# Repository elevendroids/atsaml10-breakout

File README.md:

# ATSAML1x Breakout Board (Rev. A)

Small breakout board designed for the [ATSAML10 and ATSAML11](https://ww1.microchip.com/downloads/en/DeviceDoc/SAM-L10L11-Family-DataSheet-DS60001513F.pdf) ARM Cortex-M23 MCUs from Microchip

## Features

- minimal subset of components, no power regulation etc.
- optional external main and real-time crystals - if not used, their GPIO pins can be connected to the user header by soldering relevant 0R resistors (see schematic)
- two buffered user LEDs, connected to the header - no reserved GPIOs
- reset button
- standard 0.05" pitch SWD programming header, SWD signals also present on the pin headers

Designed in KiCad 5.1.6

Schematic: [PDF](docs/atsaml10-breakout.pdf)

License: [CC BY-SA 4.0](https://creativecommons.org/licenses/by-sa/4.0/)

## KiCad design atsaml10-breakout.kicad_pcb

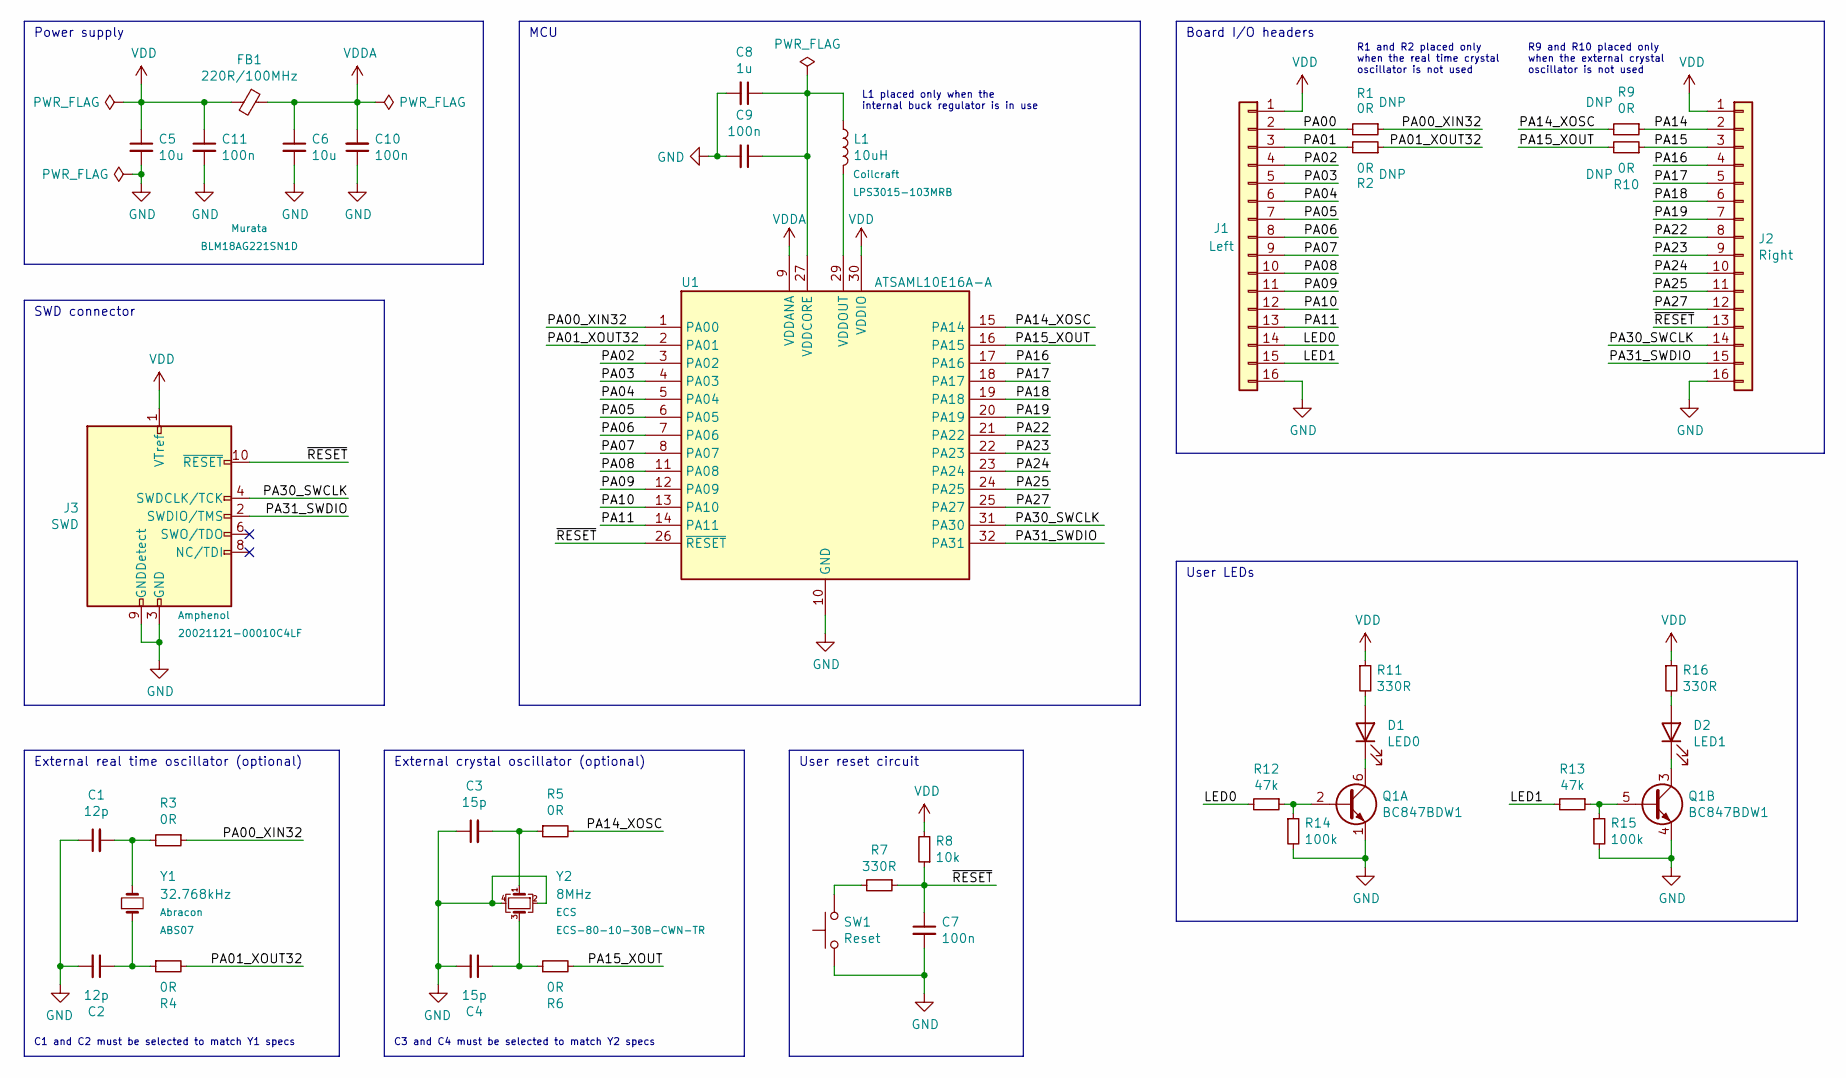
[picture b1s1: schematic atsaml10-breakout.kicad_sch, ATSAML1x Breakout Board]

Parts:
C1, C2: 12p; C_0603_1608Metric
C3, C4: 15p; C_0603_1608Metric
C5, C6: 10u; C_0805_2012Metric
C7, C9, C10, C11: 100n; C_0603_1608Metric
C8: 1u; C_0603_1608Metric
D1: LED0; LED_0805_2012Metric
D2: LED1; LED_0805_2012Metric
FB1: 220R/100MHz; L_0603_1608Metric; MPN BLM18AG221SN1D
J1: Left; PinHeader_1x16_P2.54mm_Vertical
J2: Right; PinHeader_1x16_P2.54mm_Vertical
J3: SWD; PinHeader_2x05_P1.27mm_Vertical_SMD; MPN 20021121-00010C4LF
L1: 10uH; L_Coilcraft_LPS3015; MPN LPS3015-103MRB
Q1: BC847BDW1; SOT-363_SC-70-6
R1, R2, R3, R4, R5, R6, R9, R10: 0R; R_0402_1005Metric
R7, R11, R16: 330R; R_0603_1608Metric
R8: 10k; R_0603_1608Metric
R12, R13: 47k; R_0603_1608Metric
R14, R15: 100k; R_0603_1608Metric
SW1: Reset; SW_SPST_CK_RS282G05A3
U1: ATSAML10E16A-A; TQFP-32_7x7mm_P0.8mm
Y1: 32.768kHz; Crystal_SMD_3215-2Pin_3.2x1.5mm; MPN ABS07
Y2: 8MHz; Crystal_SMD_5032-4Pin_5.0x3.2mm; MPN ECS-80-10-30B-CWN-TR

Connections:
/LED0: J1.14, R12.2
/LED1: J1.15, R13.2
/PA00: J1.2, R1.2
/PA00_XIN32: R1.1, R3.1, U1.1 (PA00)
/PA01: J1.3, R2.2
/PA01_XOUT32: R2.1, R4.2, U1.2 (PA01)
/PA02: J1.4, U1.3 (PA02)
/PA03: J1.5, U1.4 (PA03)
/PA04: J1.6, U1.5 (PA04)
/PA05: J1.7, U1.6 (PA05)
/PA06: J1.8, U1.7 (PA06)
/PA07: J1.9, U1.8 (PA07)
/PA08: J1.10, U1.11 (PA08)
/PA09: J1.11, U1.12 (PA09)
/PA10: J1.12, U1.13 (PA10)
/PA11: J1.13, U1.14 (PA11)
/PA14: J2.2, R9.1
/PA14_XOSC: R5.2, R9.2, U1.15 (PA14)
/PA15: J2.3, R10.1
/PA15_XOUT: R6.2, R10.2, U1.16 (PA15)
/PA16: J2.4, U1.17 (PA16)
/PA17: J2.5, U1.18 (PA17)
/PA18: J2.6, U1.19 (PA18)
/PA19: J2.7, U1.20 (PA19)
/PA22: J2.8, U1.21 (PA22)
/PA23: J2.9, U1.22 (PA23)
/PA24: J2.10, U1.23 (PA24)
/PA25: J2.11, U1.24 (PA25)
/PA27: J2.12, U1.25 (PA27)
/PA30_SWCLK: J2.14, J3.4 (SWDCLK/TCK), U1.31 (PA30)
/PA31_SWDIO: J2.15, J3.2 (SWDIO/TMS), U1.32 (PA31)
/~RESET: C7.1, J2.13, J3.10 (~RESET), R7.1, R8.1, U1.26 (~RESET)
GND: C1.1, C2.2, C3.1, C4.2, C5.2, C6.2, C7.2, C8.2, C9.2, C10.1, C11.2, J1.16, J2.16, J3.3 (GND), J3.5 (GND), J3.9 (GNDDetect), Q1.1 (E1), Q1.4 (E2), R14.2, R15.2, SW1.1, U1.10 (GND), U1.28 (GND), Y2.2, Y2.4
unnamed: C1.2, R3.2, Y1.2
unnamed: C2.1, R4.1, Y1.1
unnamed: C3.2, R5.1, Y2.1
unnamed: C4.1, R6.1, Y2.3
unnamed: C8.1, C9.1, L1.1, U1.27 (VDDCORE)
unnamed: D1.1 (K), Q1.6 (C1)
unnamed: D1.2 (A), R11.2
unnamed: D2.1 (K), Q1.3 (C2)
unnamed: D2.2 (A), R16.2
unnamed: L1.2, U1.29 (VDDOUT)
unnamed: Q1.2 (B1), R12.1, R14.1
unnamed: Q1.5 (B2), R13.1, R15.1
unnamed: R7.2, SW1.2
VDD: C5.1, C11.1, FB1.2, J1.1, J2.1, J3.1 (VTref), R8.2, R11.1, R16.1, U1.30 (VDDIO)
VDDA: C6.1, C10.2, FB1.1, U1.9 (VDDANA)

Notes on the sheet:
L1 placed only when the internal buck regulator is in use
MCU
Power supply
User LEDs
C3 and C4 must be selected to match Y2 specs
SWD connector
User reset circuit
Board I/O headers
R1 and R2 placed only when the real time crystal oscillator is not used
C1 and C2 must be selected to match Y1 specs
R9 and R10 placed only when the external crystal oscillator is not used
External real time oscillator (optional)
External crystal oscillator (optional)

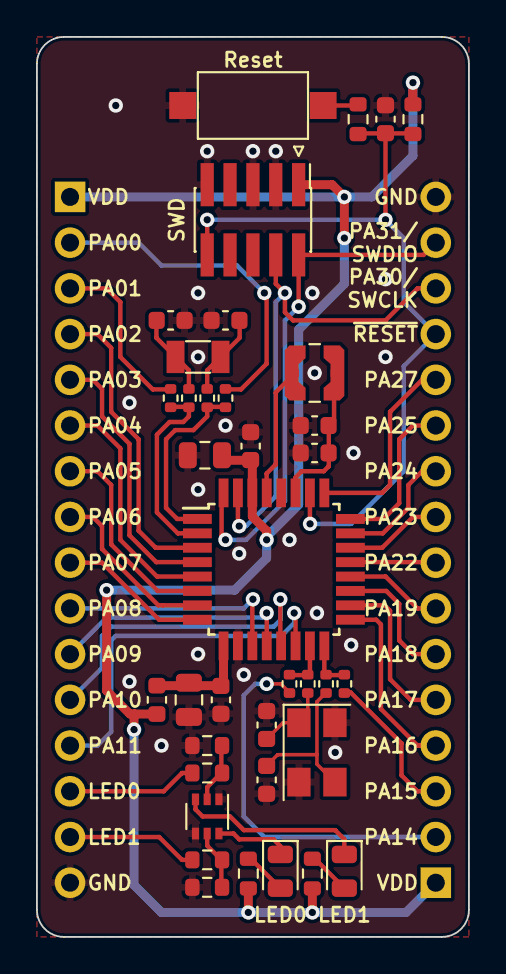
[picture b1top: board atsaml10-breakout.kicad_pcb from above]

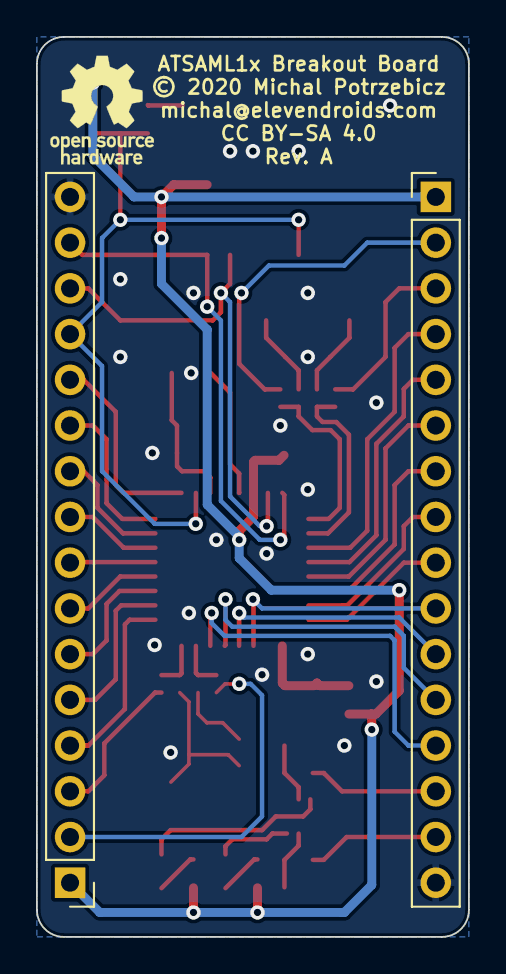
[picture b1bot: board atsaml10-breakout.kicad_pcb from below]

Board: 2 copper layers, 24.0 x 50.0 mm, 39 parts (2 on the bottom side), 48 nets.

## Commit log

2020-07-28 Initial commit, schematics almost complete
2020-07-28 Layout almost finished, added 2 LEDs, footprints tweaking
    Added two LEDs with simple transistor buffers connected to last two
    unused pins. They can be used for debugging, as indicators etc.
    Replaced C5 and C6 with 0805 parts as 10uF capacitors in 0603 are
    expensive.
    L1 footprint needs to be replaced as there are no matching 10uH
    inductors in 0603 case.
2020-07-31 Replaced L1's footprint with Coilcraft LPS3015
2020-08-01 More layout tweaks
2020-08-01 Tweaked copper pour zones settings
2020-08-02 Schematic cleanup, more PCB tweaks
2020-08-14 PCB size tweaks, align headers to 0.1" grid
2020-09-14 Getting revision A ready
    - Replaced Q1 and Q2 with BC847BDW1 and moved the chip to the front
    layer
    - Replaced 0R resistors' packages with 0402
    - Filled MFR and MPN fields for some parts
    - Added DNP fields for the option jumpers
2020-09-14 Interactive BOM
2020-09-15 Replaced Y2 footprint with a generic one
2020-09-15 Replaced Y1 footprint with a generic one
2020-09-15 Added license file
2020-09-15 Added README and a PCB render
2020-09-15 Cropped the PCB render a bit
2022-04-02 Project upgrade to KiCad 6

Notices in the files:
atsaml10-breakout.kicad_pcb:
© 2020 Michal Potrzebicz
CC BY-SA 4.0
